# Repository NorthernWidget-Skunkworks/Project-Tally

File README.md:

# Project-Tally
A minimal ultra low power digital event counter, designed to be a counterpart to a traditional data logger to measure and average rapid events like an anemometer reading

## Features:
- On board super capacitor (can be self powered between readings/recharge) 
- Extreme low power 
- 3.3/5v capable 
- I2C interface
- Measure up to 65536 (2^16) events before rollover
- Integrated input pullup/pulldown
- Integrated input conditioning (allows for non-binary inputs)

Using jumpers on bottom side of board, can configure input as pullup, pulldown (ultra low power mode), or direct input if driving from another device

### Connectivity:
Device can easily be interfaced to using I2C at either 3.3v or 5v (logic and power). 

A library has been developed for interfacing with Arduino based devices:
[Tally Library](https://github.com/NorthernWidget-Skunkworks/Tally_Library)
### Power Consumption: 

| Mode | Current @ 3.3v | 
| ---- | ------------- |
| Default | ~4mA |
| Sleep | <100uA |
| Switched | N/A<sup>1</sup> |

<sup>1</sup>When the device is disconnected from the power bus, it draws no external power and runs off the on board super cap. Tested in pull up mode with 100Hz, 50% duty cycle switching input. Ran for 30 minutes, resulting in a consumption of ~ 0.275J of energy = 7.64e-5 Watt Hours -> 15.26 uW avg -> ~ 5uA @ 3v avg. 

#### Maximum input frequency: 

| Mode | Max Freq [kHz] | 
| ---- | ------------- |
| Pull Up | 16 |
| Pull Down | 10 |
| Direct, Square | 9 |
| Direct, Sine | 22 |
| Direct, Triangle | 22 |

Measured using a function generator with a 2.5v amplitude for push pull tests, and driving an appropriately selected MOSFET for the pull up and pull down variations to act as an analogous switch, once again driven by a function generator. 

---

> ##### ***"Errors using inadequate data are much less than those using no data at all."***
> - **[Charles Babbage](https://en.wikipedia.org/wiki/Charles_Babbage)**

**Concept and design by [Bobby Schulz](https://github.com/bschulz1701) at Northern Widget**

<br>
<br />This work is licensed under a <a rel="license" href="http://creativecommons.org/licenses/by-sa/4.0/">Creative Commons Attribution-ShareAlike 4.0 International License</a>.

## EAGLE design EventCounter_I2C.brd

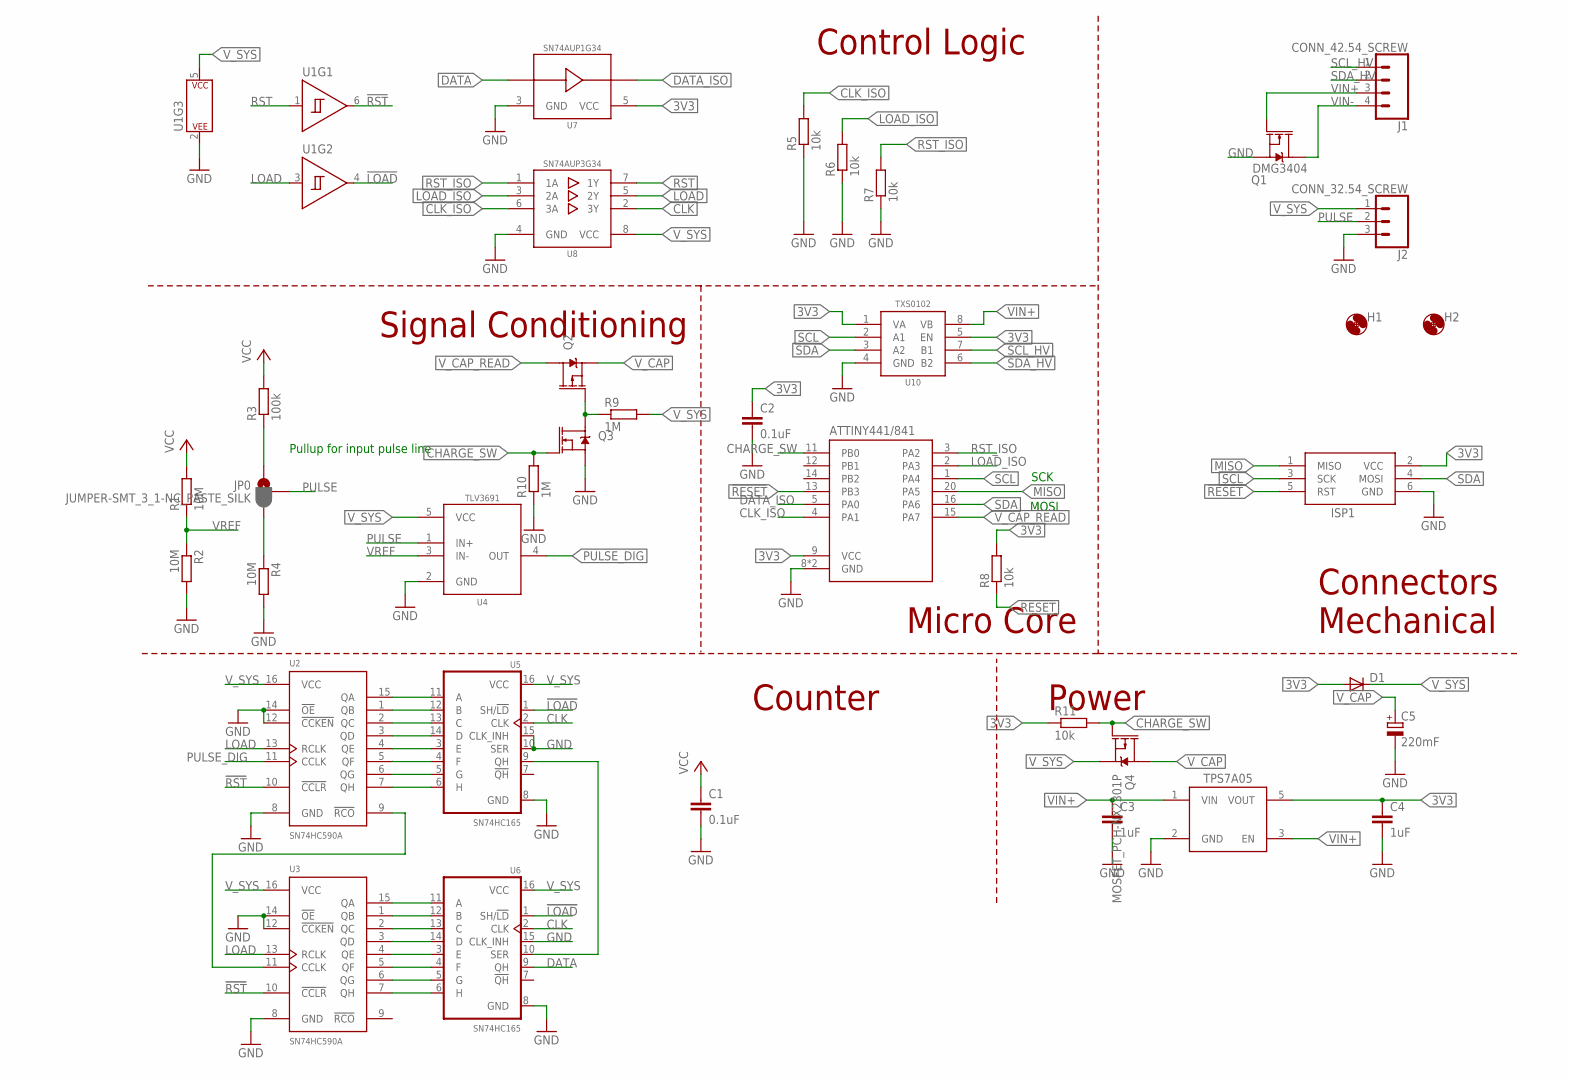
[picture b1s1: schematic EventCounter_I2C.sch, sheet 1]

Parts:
C1, C2: 0.1uF; C0402
C3, C4: 1uF; C0603
C5: 220mF; HL; MPN DSK-3R3H224U-HL; DIGIKEY 604-1020-1-ND
D1: DIODESOD-123; SOD-123; MPN BAT43W-7-F; DIGIKEY BAT43W-FDICT-ND
H1, H2: MOUNTING_HOLE2_NP; 2_56
ISP1: AVRISP1.27MM; 2X3_1.27
J1: CONN_42.54_SCREW; 1X04_SCREW
J2: CONN_32.54_SCREW; 1X03_SCREW
JP0: JUMPER-SMT_3_1-NC_PASTE_SILK; SMT-JUMPER_3_1-NC_PASTE_SILK
Q1: DMG3404; SOT23-3
Q2: MOSFET_PCH-RZM001P02; SOT723
Q3: MOSFET-NCH-RE1C002UN; SC-89
Q4: MOSFET_PCH-NX2301P; SOT23-3
R1, R2, R4: 10M; R0603
R3: 100k; R0603
R5, R6, R7, R8, R11: 10k; R0402
R9, R10: 1M; R0402
U1: SN74AUP2G14SC70; DCK_R-PDSO-G6
U2, U3: SN74HC590AD; SO16
U4: TLV3691DCK; DCK_R-PDSO-G5
U5, U6: SN74HC165PW; TSSOP16
U7: SN74AUP1G34SC70; DCK_R-PDSO-G5
U8: SN74AUP3G34DCU; DCU_(R-PDSO-G8)
U9: ATTINY441/841VQFN; VQFN-20
U10: TXS0102DQM; DQM_R-PX2SON-N8
U11: TPS7A0533DBV; SOT23-5

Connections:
3V3: C2.1, C4.1, D1.ANODE (A), ISP1.2 (VCC), R8.2, R11.1, U7.5 (VCC), U9.9 (VCC), U10.1 (VA), U10.5 (EN), U11.5 (VOUT)
!LOAD: U1.4 (Y), U5.1 (SH/!LD), U6.1 (SH/!LD)
!RESET: ISP1.5 (RST), R8.1, U9.13 (PB3)
!RST: U1.6 (Y), U2.10 (!CCLR), U3.10 (!CCLR)
CHARGE_SW: Q3.1 (G), Q4.1 (G), R10.2, R11.2, U9.11 (PB0)
CLK: U5.2 (CLK), U6.2 (CLK), U8.2 (3Y)
CLK_ISO: R5.2, U8.6 (3A), U9.4 (PA1)
DATA: U6.9 (QH), U7.2 (A)
DATA_ISO: U7.4 (Y), U9.5 (PA0)
GND: C1.2, C2.2, C3.2, C4.2, C5.-, ISP1.6 (GND), J2.3, Q1.2 (S), Q3.2 (S), R2.2, R4.2, R5.1, R6.1, R7.1, R10.1, U1.2 (P$V-), U2.8 (GND), U2.12 (!CCKEN), U2.14 (!OE), U3.8 (GND), U3.12 (!CCKEN), U3.14 (!OE), U4.2 (GND), U5.8 (GND), U5.10 (SER), U5.15 (CLK_INH), U6.8 (GND), U6.15 (CLK_INH), U7.3 (GND), U8.4 (GND), U9.8 (GND), U9.EP (GND), U10.4 (GND), U11.2 (GND)
LOAD: U1.3 (A), U2.13 (RCLK), U3.13 (RCLK), U8.5 (2Y)
LOAD_ISO: R6.2, U8.3 (2A), U9.2 (PA3)
MISO: ISP1.1 (MISO), U9.20 (PA5)
unnamed: U3.15 (QA), U6.11 (A)
unnamed: U3.1 (QB), U6.12 (B)
unnamed: U3.2 (QC), U6.13 (C)
unnamed: U3.3 (QD), U6.14 (D)
unnamed: U3.4 (QE), U6.3 (E)
unnamed: U3.5 (QF), U6.4 (F)
unnamed: U3.6 (QG), U6.5 (G)
unnamed: U3.7 (QH), U6.6 (H)
unnamed: U2.7 (QH), U5.6 (H)
unnamed: U2.6 (QG), U5.5 (G)
unnamed: U2.5 (QF), U5.4 (F)
unnamed: U2.4 (QE), U5.3 (E)
unnamed: U2.3 (QD), U5.14 (D)
unnamed: U2.2 (QC), U5.13 (C)
unnamed: U2.1 (QB), U5.12 (B)
unnamed: U2.15 (QA), U5.11 (A)
unnamed: U5.9 (QH), U6.10 (SER)
unnamed: U2.9 (!RCO), U3.11 (CCLK)
unnamed: JP0.3, R4.1
unnamed: JP0.1, R3.1
unnamed: Q2.1 (G), Q3.3 (D), R9.1
PULSE: J2.2, JP0.2, U4.1 (IN+)
PULSE_DIG: U2.11 (CCLK), U4.4 (OUT)
RST: U1.1 (A), U8.7 (1Y)
RST_ISO: R7.2, U8.1 (1A), U9.3 (PA2)
SCL: ISP1.3 (SCK), U9.1 (PA4), U10.2 (A1)
SCL_HV: J1.1, U10.7 (B1)
SDA: ISP1.4 (MOSI), U9.16 (PA6), U10.3 (A2)
SDA_HV: J1.2, U10.6 (B2)
VIN+: C3.1, J1.3, Q1.1 (G), U10.8 (VB), U11.1 (VIN), U11.3 (EN)
VIN-: J1.4, Q1.3 (D)
VREF: R1.1, R2.1, U4.3 (IN-)
V_CAP: C5.+, Q2.2 (S), Q4.3 (D)
V_CAP_READ: Q2.3 (D), U9.15 (PA7)
V_SYS: C1.1, D1.CAT (C), J2.1, Q4.2 (S), R1.2, R3.2, R9.2, U1.5 (P$V+), U2.16 (VCC), U3.16 (VCC), U4.5 (VCC), U5.16 (VCC), U6.16 (VCC), U8.8 (VCC)

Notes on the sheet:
Pullup for input pulse line
Counter
Control Logic
Connectors Mechanical
MOSI
SCK
Power
Micro Core
Signal Conditioning

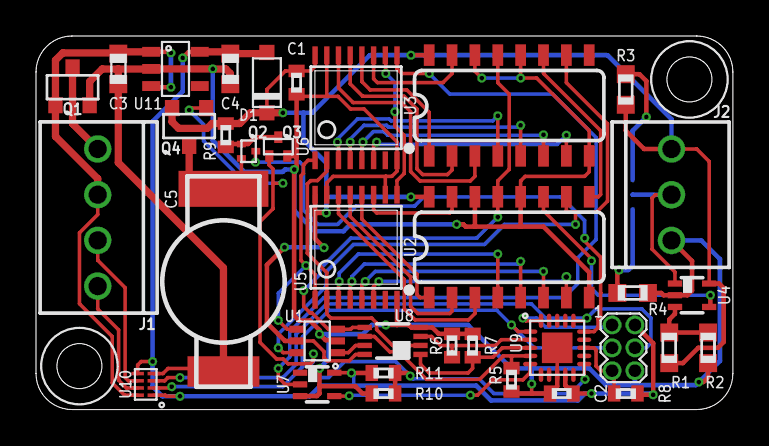
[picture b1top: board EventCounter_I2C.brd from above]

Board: 2 copper layers, 38.7 x 20.8 mm, 38 parts (1 on the bottom side), 48 nets.

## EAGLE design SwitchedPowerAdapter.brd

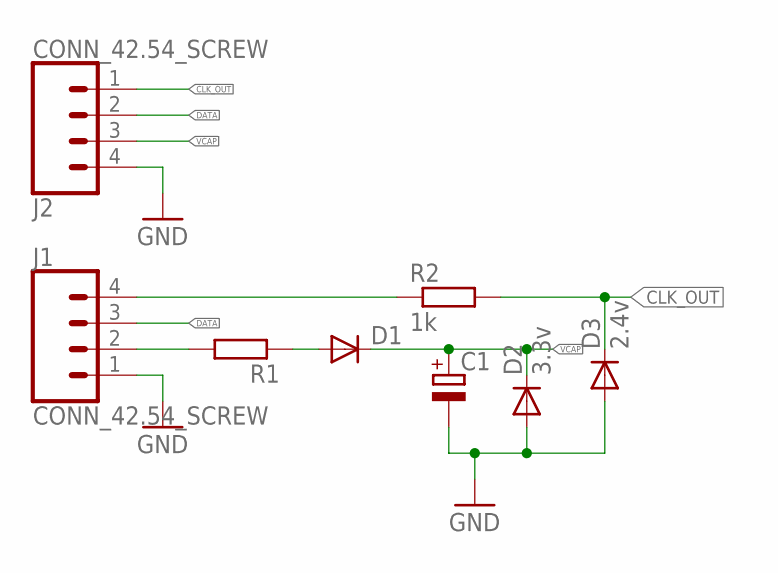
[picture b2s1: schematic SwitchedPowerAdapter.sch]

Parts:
C1: CPOL-EUHL; HL
D1: DIODEDO-214AC; DO214AC; MPN S1A; DIGIKEY S1AFSCT-ND
D2: 3.3v; SOD-123; MPN MMSZ4683-HE3-08; DIGIKEY MMSZ4683-HE3-08GICT-ND
D3: 2.4v; SOD-123
J1, J2: CONN_42.54_SCREW; 1X04_SCREW
R1: R-EU_R2512; R2512
R2: 1k; R0402

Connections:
CLK: J1.4, R2.1
CLK_OUT: D3.CAT (C), J2.1, R2.2
DATA: J1.3, J2.2
GND: C1.-, D2.ANODE (A), D3.ANODE (A), J1.1, J2.4
unnamed: J1.2, R1.2
unnamed: D1.A, R1.1
VCAP: C1.+, D1.C, D2.CAT (C), J2.3

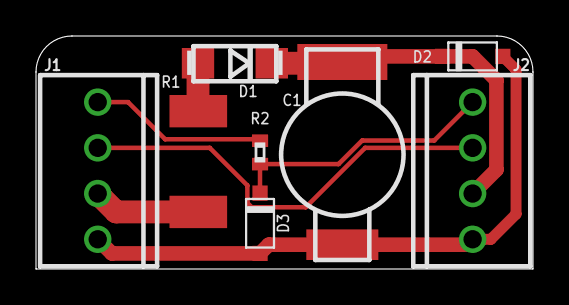
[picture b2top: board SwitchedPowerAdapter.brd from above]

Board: 2 copper layers, 27.6 x 12.9 mm, 8 parts (0 on the bottom side), 7 nets.

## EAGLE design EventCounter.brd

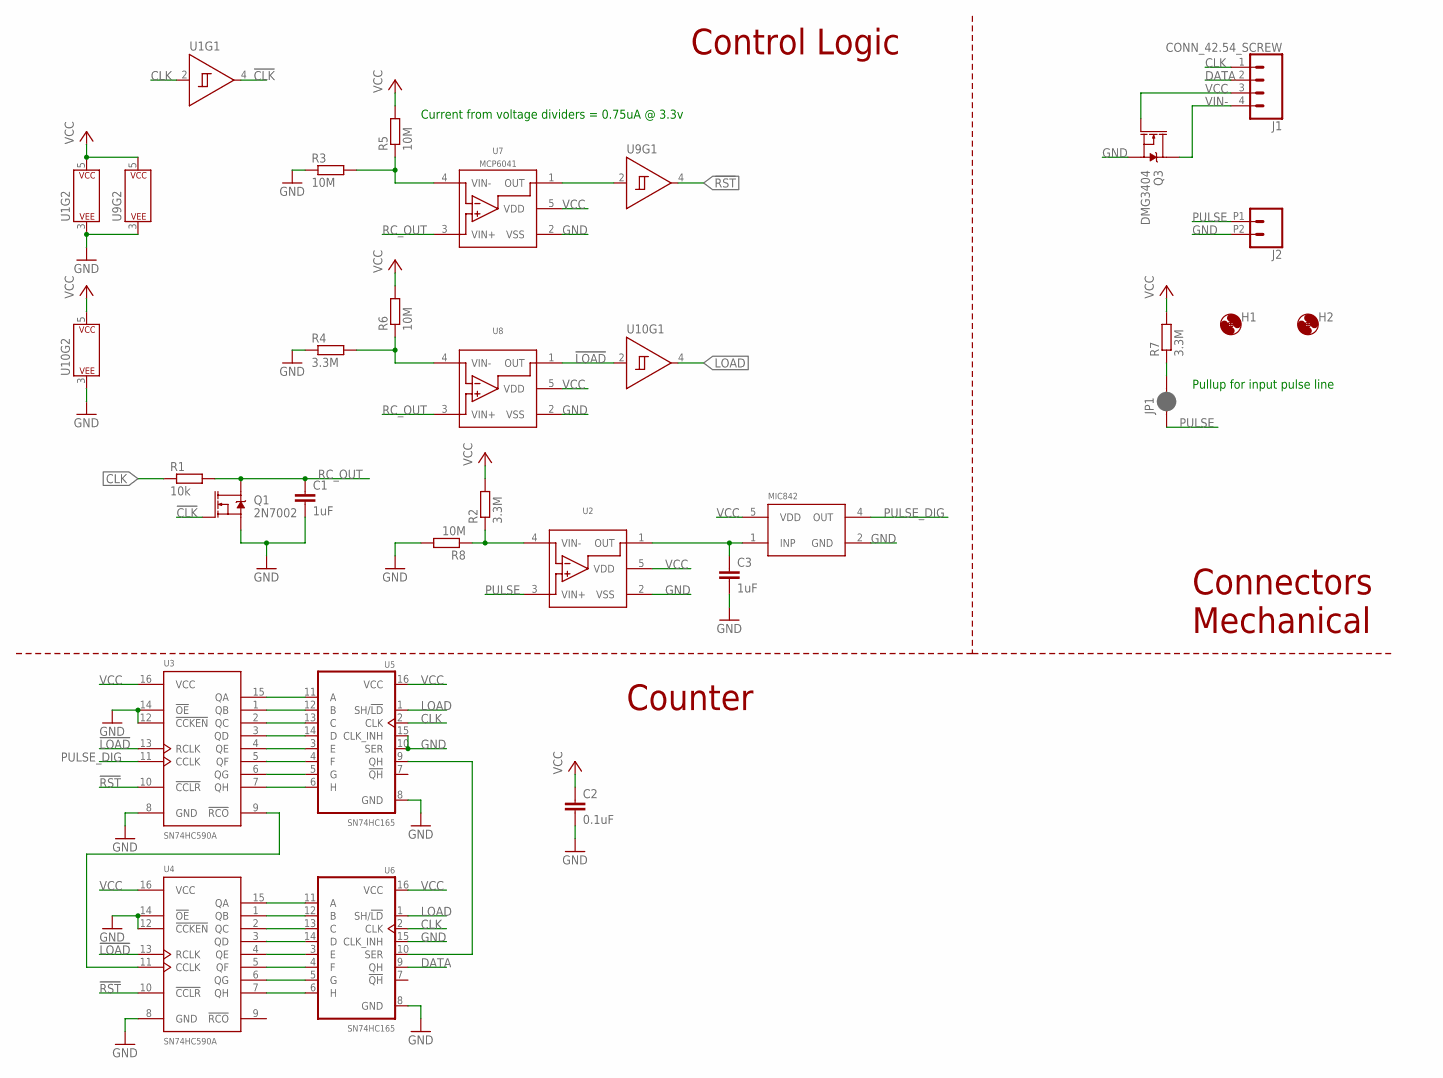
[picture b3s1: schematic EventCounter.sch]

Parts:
C1, C3: 1uF; C0603
C2: 0.1uF; C0603
H1, H2: MOUNTING_HOLE2_NP; 2_56
J1: CONN_42.54_SCREW; 1X04_SCREW
J2: CONN_02SCREW_2.54; 1X02_2.54_SCREWTERM
JP1: JUMPER-SMT_2_NC_PASTE_SILK; SMT-JUMPER_2_NC_PASTE_SILK
Q1: 2N7002; SOT323
Q3: DMG3404; SOT23-3
R1: 10k; R0603
R2, R4, R7: 3.3M; R0603
R3, R5, R6, R8: 10M; R0603
U1, U9, U10: SN74LVC1G14DCK; DCK_R-PDSO-G5
U2, U7, U8: MCP6041; SOT23-5
U3, U4: SN74HC590AD; SO16
U5, U6: SN74HC165D; SO16
U$1: MIC842H; DCK_R-PDSO-G5

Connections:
!CLK: Q1.1 (G), U1.4 (Y)
!LOAD: U3.13 (RCLK), U4.13 (RCLK), U8.1 (OUT), U10.2 (A)
!RST: U3.10 (!CCLR), U4.10 (!CCLR), U9.4 (Y)
CLK: J1.1, R1.1, U1.2 (A), U5.2 (CLK), U6.2 (CLK)
DATA: J1.2, U6.9 (QH)
GND: C1.2, C2.2, C3.2, J2.P2 (2), Q1.2 (S), Q3.2 (S), R3.1, R4.1, R8.2, U1.3 (P$V-), U2.2 (VSS), U3.8 (GND), U3.12 (!CCKEN), U3.14 (!OE), U4.8 (GND), U4.12 (!CCKEN), U4.14 (!OE), U5.8 (GND), U5.10 (SER), U5.15 (CLK_INH), U6.8 (GND), U6.15 (CLK_INH), U7.2 (VSS), U8.2 (VSS), U9.3 (P$V-), U10.3 (P$V-), U$1.2 (GND)
LOAD: U5.1 (SH/!LD), U6.1 (SH/!LD), U10.4 (Y)
unnamed: U4.15 (QA), U6.11 (A)
unnamed: U4.1 (QB), U6.12 (B)
unnamed: U4.2 (QC), U6.13 (C)
unnamed: U4.3 (QD), U6.14 (D)
unnamed: U4.4 (QE), U6.3 (E)
unnamed: U4.5 (QF), U6.4 (F)
unnamed: U4.6 (QG), U6.5 (G)
unnamed: U4.7 (QH), U6.6 (H)
unnamed: U3.7 (QH), U5.6 (H)
unnamed: U3.6 (QG), U5.5 (G)
unnamed: U3.5 (QF), U5.4 (F)
unnamed: U3.4 (QE), U5.3 (E)
unnamed: U3.3 (QD), U5.14 (D)
unnamed: U3.2 (QC), U5.13 (C)
unnamed: U3.1 (QB), U5.12 (B)
unnamed: U3.15 (QA), U5.11 (A)
unnamed: U5.9 (QH), U6.10 (SER)
unnamed: U3.9 (!RCO), U4.11 (CCLK)
unnamed: R2.1, R8.1, U2.4 (VIN-)
unnamed: JP1.2, R7.1
unnamed: R4.2, R6.1, U8.4 (VIN-)
unnamed: C3.1, U2.1 (OUT), U$1.1 (INP)
unnamed: R3.2, R5.1, U7.4 (VIN-)
PULSE: J2.P1 (1), JP1.1, U2.3 (VIN+)
PULSE_DIG: U3.11 (CCLK), U$1.4 (OUT)
RC_OUT: C1.1, Q1.3 (D), R1.2, U7.3 (VIN+), U8.3 (VIN+)
RST: U7.1 (OUT), U9.2 (A)
VCC: C2.1, J1.3, Q3.1 (G), R2.2, R5.2, R6.2, R7.2, U1.5 (P$V+), U2.5 (VDD), U3.16 (VCC), U4.16 (VCC), U5.16 (VCC), U6.16 (VCC), U7.5 (VDD), U8.5 (VDD), U9.5 (P$V+), U10.5 (P$V+), U$1.5 (VDD)
VIN-: J1.4, Q3.3 (D)

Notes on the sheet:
Pullup for input pulse line
Counter
Control Logic
Connectors Mechanical
Current from voltage dividers = 0.75uA @ 3.3v

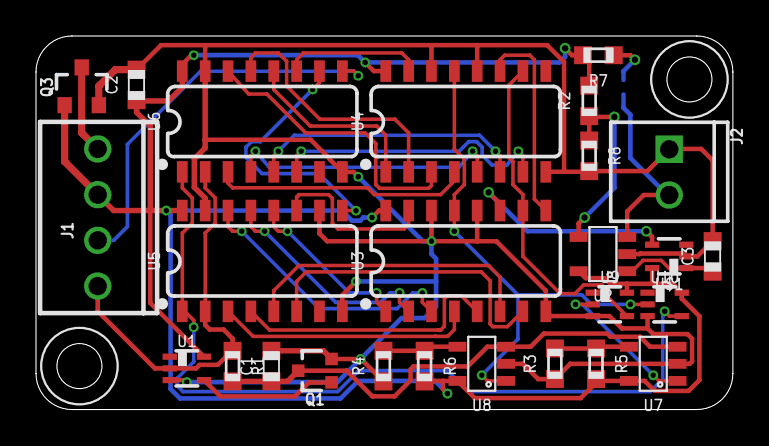
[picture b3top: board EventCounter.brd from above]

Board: 2 copper layers, 38.7 x 20.8 mm, 29 parts (1 on the bottom side), 36 nets.

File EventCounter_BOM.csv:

"Qty";"Value";"Device";"Package";"Parts";"Description";"DIGIKEY";"DISP";"MF";"MPN";"PROD_ID";"VALUE";"VALUE_PART";
"1";"";"CONN_02SCREW_2.54";"1X02_2.54_SCREWTERM";"J2";"Multi connection point. Often used as Generic Header-pin footprint for 0.1 inch spaced/style header connections";"ED10561-ND";"";"OnShore";"OSTVN02A150";"";"";"";
"2";"";"MOUNTING_HOLE2_NP";"2_56";"H1, H2";"Genaric Mechanical Mounting Hole";"";"";"";"";"";"";"";
"2";"";"SN74HC165D";"SO16";"U5, U6";"SN74HC165 - 8 bit PISO shift register";"296-8250-1-ND";"";"TI";"SN74HC165DR";"";"";"";
"2";"";"SN74HC590AD";"SO16";"U3, U4";"SN74HC590A - 8 bit binary counter with direct clear";"296-8340-5-ND";"";"TI";"SN74HC590AD";"";"";"";
"3";"";"SN74LVC1G14DCK";"DCK_R-PDSO-G5";"U1, U9, U10";"SN74x1G14 - Single Schmitt Triger Inverter";"296-11608-1-ND";"";"TI";"SN74LVC1G14DCKR";"";"";"";
"1";"0.1uF";"C-EU0.1UFC0603";"C0603";"C2";"CAPACITOR, European symbol";"490-6051-1-ND";"";"Murata";"GCM188R71E104KA57D";"";"";"";
"3";"10M";"R-EU_10MR0603";"R0603";"R3, R5, R6";"RESISTOR, European symbol";"311-10.0MHRCT-ND";"";"Yageo";"RC0603FR-0710ML";"";"";"10M";
"2";"10k";"R-EU_10KR0603";"R0603";"R1, R7";"RESISTOR, European symbol";"311-10.0KHRCT-ND";"";"Yageo";"RC0603FR-0710KL";"";"";"10k";
"1";"1uF";"C-EU1UFC0603";"C0603";"C1";"CAPACITOR, European symbol";"1276-6524-1-ND";"";"Samsung";"1276-6524-1-ND";"";"";"";
"1";"2N7002";"MOSFET-NCH-2N7002PW";"SOT323";"Q1";"N-channel MOSFETs";"2N7002W-FDICT-ND";"";"Diodes Incorporated";"2N7002W-7-F";"TRANS-11151";"2N7002";"";
"1";"3.3M";"R-EU_3.3MR0603";"R0603";"R4";"RESISTOR, European symbol";"RMCF0603FT3M30CT-ND";"";"Stackpole";"RMCF0603FT3M30";"";"";"3.3M";
"1";"CONN_42.54_SCREW";"CONN_42.54_SCREW";"1X04_SCREW";"J1";"Genaric 4 pin connector";"";"";"";"";"";"";"";
"1";"DMG3404";"MOSFET-NCH-DMG3404L";"SOT23-3";"Q3";"N-channel MOSFETs";"DMG3404L-7DICT-ND";"";"Diodes Incorporated";"DMG3404L-7";"";"DMG3404";"";
"1";"JUMPER-SMT_2_NC_PASTE_SILK";"JUMPER-SMT_2_NC_PASTE_SILK";"SMT-JUMPER_2_NC_PASTE_SILK";"JP1";"Normally closed solder jumper";"";"";"";"";"";"";"";
"2";"MCP6041";"MCP6041";"SOT23-5";"U7, U8";"MCP6041 - Low Power Rail to Rail Op-Amp";"MCP6041T-I/OTCT-ND";"MCP6041";"Microchip";"MCP6041T-I/OT";"";"";"";

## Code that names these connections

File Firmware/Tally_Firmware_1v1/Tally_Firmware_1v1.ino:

/******************************************************************************
Tally_Firmware_1v1.ino
Driver for Tally event counter
Bobby Schulz @ Northern Widget LLC
5/16/2019
https://github.com/NorthernWidget-Skunkworks/Project-Tally

This firmware is to be run on the I2C capable Tally v1.1 in order to allow for interface, control, and data collection 

Firmware Version: 0.2.0

"On two occasions I have been asked, 'Pray, Mr. Babbage, if you put into the machine wrong figures, will the right answers come out?' 
I am not able rightly to apprehend the kind of confusion of ideas that could provoke such a question."
-Charles Babbage

Distributed as-is; no warranty is given.
******************************************************************************/

#include <avr/sleep.h>
#include <avr/power.h>
#include <avr/interrupt.h>
#include "WireS.h"
#define DATA_PIN 10
#define CLK_PIN 9
#define RST_PIN 8
#define LOAD_PIN 7
#define CHARGE_SW 0
#define V_CAP_READ A7

#define CHIP_ID_CALL 0xD0
#define CHIP_ID 0xB0
#define FIRMWARE_NUM 2

uint8_t ADR = 0x33; //DUMMY! FIX! and make changable

// volatile bool GenCall = false; //Flag for generic address call over I2C //FIX! add generalizable address

uint8_t Config = 0; //Global config value
uint8_t Reg[5] = {0}; //Initialize registers
const uint8_t RegLen = sizeof(Reg); //Number of registers in Reg
bool Sample = false; //Flag to get a new sample value
bool Reset = false; //Reset flag
bool Clear = false; //Clear registers
bool Peek = false; //Clear values on read by default
bool Sleep = false; //Do not sleep by default
bool ReadCap = false; //Read float voltage of capacitor 
bool NoCap = false; //Disconnect capacitor, this will be reset on POR

volatile bool StopFlag = false; //Used to indicate a stop condition 
volatile uint8_t RegID = 0; //Used to denote which register will be read from
volatile bool RepeatedStart = false; //Used to show if the start was repeated or not

const unsigned long WAIT_TIME = 100; //Genric wait cycle after read operation, keep device alive for repeated requests

void setup() {
	pinMode(DATA_PIN, INPUT); //Setup GPIO interface pins
	pinMode(CLK_PIN, OUTPUT);
	pinMode(RST_PIN, OUTPUT);
	pinMode(LOAD_PIN, OUTPUT);
	pinMode(CHARGE_SW, OUTPUT);
	ReadVoltage(); //Get voltage on startup, available to read afterwards 
	digitalWrite(CHARGE_SW, LOW); //By default have system charging 

	Wire.begin(ADR);  //Begin slave I2C FIX! Add variable address feature!

	//Setup I2C slave
	Wire.onAddrReceive(AddressEvent); 
	Wire.onRequest(RequestEvent);    
	Wire.onReceive(ReceiveEvent);
	Wire.onStop(StopEvent);
}

void loop() {

	if(Sleep) { //Put device to sleep on wrap arround
		ADCSRA &= ~(1<<ADEN); //Disable ADC
		SPCR   &= ~_BV(SPE); //Disable SPI
		//    PRR = 0xFF;
			set_sleep_mode(SLEEP_MODE_PWR_DOWN);  

		sleep_enable();
		sleep_mode(); //Waits here while in sleep mode

		sleep_disable(); //Wake up
		TWSCRA = bit(TWEN);  //Re-enable I2C
		Wire.begin(ADR);
	}

	int Counter = 0; //Run cycles after wakeup
	while(++Counter < WAIT_TIME) {
		Sample = BitRead(Reg[0], 0);
		Clear = BitRead(Reg[0], 1);
		Reset = BitRead(Reg[0], 2);
		Peek = BitRead(Reg[0], 3);
		Sleep = BitRead(Reg[0], 4); 
		ReadCap = BitRead(Reg[0], 5);
		NoCap = BitRead(Reg[0], 6);

		if(Sample) {
			SplitAndLoad(1, GetTicks()); //Load tick value into register 1
			if(!Peek) ClearTicks(); //Clear counter values if peak is disabled
			Reg[0] = Reg[0] & 0xFE; //Clear sample bit in register
			Sample = false; //Clear sample bit
		}
		if(Reset) { //Software reset of system
			ClearTicks();
			Reg[1] = 0x00; //Clear registers
			Reg[2] = 0x00;
			Reg[0] = Reg[0]; //Reset to POR
			Clear = false; //Clear flag
		}
		if(Clear) {
			ClearTicks(); //Clear registers 
			Reg[0] = Reg[0] & 0xFD; //Clear CLEAR bit
			Reset = false; //Clear flag
		}

		if(ReadCap) {
			ReadVoltage(); //Read voltage and load into I2C regs
			Reg[0] = Reg[0] & 0xDF; //Clear Voltage Read bit
			ReadCap = false; //Clear flag
		}

		if(NoCap) {
			digitalWrite(CHARGE_SW, HIGH); //Disconnect cap from Vin
		}

		if(!NoCap) {
			digitalWrite(CHARGE_SW, LOW); //Connect cap to Vin
		}
		delay(1); //Wait during wake/I2C transaction 
	}
	Counter = 0; //Clear counter to either go to sleep or wrap around
}

void SplitAndLoad(uint8_t Pos, unsigned int Val) //Write 16 bits
{
	uint8_t Len = sizeof(Val);
	for(int i = Pos; i < Pos + Len; i++) {
		Reg[i] = (Val >> (i - Pos)*8) & 0xFF; //Pullout the next byte
	}
}

boolean AddressEvent(uint16_t Address, uint8_t count) //When a valid address is encountered on I2C
{
	// if(Address == 0x00) { //FIX! add generalizable address
	// 	GenCall = true;
	// }
	RepeatedStart = (count > 0 ? true : false);
	return true; // send ACK to master
}

void RequestEvent()  //When I2C values are requested
{	if(RegID == CHIP_ID_CALL) {
		Wire.write(CHIP_ID); //Return Chip ID if requested
		Wire.write(FIRMWARE_NUM); //Send firmware version number
	}
	else {
		for(int i = 0; i < RegLen; i++) {  
			Wire.write(Reg[(RegID + i) % RegLen]);  //Load all bytes (wrap around) into register
		}
	}
}

void ReceiveEvent(int DataLen) //When I2C values are sent 
{
    //Write data to appropriate location
    if(DataLen == 2){
	    //Remove while loop?? 
	    while(Wire.available() < 2); //Only option for writing would be register address, and single 8 bit value
	    uint8_t Pos = Wire.read();
	    uint8_t Val = Wire.read();
	    //Check for validity of write??
	    Reg[Pos] = Val; //Set register value
	}

	// if(DataLen == 1 && GenCall == true) {  //FIX! add generalizable address
	// 	ADR = Wire.read(); //Update address value 
	// }

	// if(DataLen == 1 && GenCall == false){
	// 	RegID = Wire.read(); //Read in the register ID to be used for subsequent read
	// }
	if(DataLen == 1){
		RegID = Wire.read(); //Read in the register ID to be used for subsequent read
	}
}

void StopEvent() //When stop value is detected on I2C
{
	StopFlag = true;
  	RegID = (RegID + Wire.getTransmitBytes()) % RegLen; //Increment register pointer appropriate amount
	//End comunication
}

unsigned int GetTicks() //Read number of ticks from digital logic 
{
	unsigned int Data = 0; //Number of pulses since last read
	digitalWrite(LOAD_PIN, HIGH);  //Pulse LOAD pin low to trigger load of new data
	delayMicroseconds(5); 
  	digitalWrite(LOAD_PIN, LOW); 

  	Data = digitalRead(DATA_PIN);
  	Data = Data << 1; 
	for(int i = 0; i < 15; i++) {
    digitalWrite(CLK_PIN, HIGH); //Clock new data in
		delayMicroseconds(5); //Wait to stabilize
		Data = (Data << 1) | digitalRead(DATA_PIN);
    digitalWrite(CLK_PIN, LOW); 
		delayMicroseconds(5);
	} 
	return Data;
}

void ClearTicks() //Clear digital logic values 
{
	digitalWrite(RST_PIN, HIGH);  //Pulse reset pin high for short interval to trigger reset
	delayMicroseconds(5);
  	digitalWrite(RST_PIN, LOW); 
}

bool ReadVoltage() //Read the bit value at the specified position
{
	digitalWrite(CHARGE_SW, HIGH); //Connect voltage to ADC
	delay(1); //Wait to settle FIX??
	uint16_t Val = analogRead(V_CAP_READ);
	if(!NoCap) digitalWrite(CHARGE_SW, LOW); //Disconnect and continue charging if cap is set to be nominally connected
	Reg[4] = Val >> 8; //Load MSB
	Reg[3] = Val & 0xFF; //Load LSB
}

bool BitRead(uint8_t Val, uint8_t Pos) //Read the bit value at the specified position
{
	return (Val >> Pos) & 0x01;
}

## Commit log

2018-05-22 WIP simulations for control circuitry
2018-05-22 Added simulations for new pulse length trigger
    Added simulations for some of the legacy designs for the pulse length trigger, and the new design for pulse length trigger with Monte Carlo simulations
2018-05-23 Added schematic for event counter with preliminary layout
    Schematic is essentially complete, very preliminary part placement done on board
2018-05-23 Cleaned up schematic and added frame
2018-05-24 Completed initial routing, added silk screen info
    Board is functionally complete baring cleanup or modifications, added silk screen info to bottom layer
2018-05-24 Changed passive values
    Changed the passive resistor divider values, need to verify with part availability
2018-05-25 Changed resistor divider values for low power
    After checking part availability, changed values to more logical ones
2018-06-01 Simulation cleanup
2018-06-05 Added BOM and decoupling cap
    Added BOM files and decoupling capacitor, cleaned up some silkscreen issues, ready for final review
2018-06-06 Added Gerbers, ready for first run
    Did cleanup and added reverse polarity symbol, generated gerbers, also updated gitignore to deal with LTSpice files
2018-06-28 Added input signal conditioning, added test script
    Added input signal conditioning to fix metastability problem occurring due to excessive rise times due to pullup input
2018-06-28 Updated part info, license and BOM
2018-07-10 Updated gerbers
2018-07-12 Added wind tunnel test file, needs further verification
2018-07-17 Added stencil DXF
2018-11-08 Initial layout of capacitor charge board
    Early layout of external capacitor charge board
2018-11-27 Generated gerbers, updated part number on Switched Power
2019-01-04 Const Power Adapter minor edits, generated gerbers
    Minor edits to silkscreen on Const Power Adapter and generated gerbers, submitted adapter board v0.0 to fab
2019-04-08 Added testing data and updated TallyTest to support power switching
2019-04-08 Added board dimensions and generated PDFs
2019-04-18 Added initial developments for I2C variant
    Added first cut schematic for I2C variant, needs verification and decent cleanup
2019-04-19 Initial layout for I2C variant
    First cut layout for I2C variant, passes DRC, still needs verification
2019-04-20 Minor edits, sent to fab for v1.0 (I2C model)
    Cleaned up layout, added pullup reset resistor, generated gerbers, sent v1.0 to fab
2019-04-21 Rename LICENSE.md to LICENSE
2019-04-21 CC BY-SA 4.0 International: official wording
2019-04-30 Updated values/digikey info
    Updated the part
2019-05-15 Updated firmware, minor design update
    Improved firmware capabilities, added minor design updates to schematic, routing and feature decision still required
2019-05-15 Routing and design update for v1.1
    Cleanup/verification required before sending to fab
2019-05-16 Minor cleanup, generated gerbers, sent v1.1 to fab
    Minor cleanup and rearranging silkscreen names, changed jumper configuration
2019-05-16 Firmware cleanup
2019-05-27 Added support for v1.2 I2C board in firmware
    Added support for voltage reading on the v1.2 I2C board, still need to rename/organize firmware
2019-05-29 Updated voltage read in firmware
    Added voltage read on startup, so you can read minimum voltage after cycle is completed
2019-06-06 Minor value updates
2019-06-13 Updated part values
    Switched values of `R10` and `R11`, values were erroneously switched which resulted in the capacitor being connected to the ADC input during sleep/off state, causing significant power draw
2019-06-27 Minor readme addition
2019-06-28 Updated readme with valid info
    Needs verification/correction on frequency values
2019-06-28 Updated frequency values in readme
2019-06-28 Initial test of ChipID implementation
    Testing required
2019-06-28 Attempted gitignore tracking fix
2019-06-28 Re-added CSVs, reorganized folder structure
2019-06-28 Moved regmap info into firmware folder
2019-06-28 Updated readme, added switched cap support in firmware
    Added support for switched capacitor and changed naming of `reset` and `clear` to match that of software library
2019-06-28 Updated readme with test info
2019-07-03 Added firmware report
2020-04-30 Stencil flat surface for solder-paste application
2020-05-01 Definitely not noncommercial; wrong text in license file!
2020-05-01 GNU GPL v3 for code products (software, firmware, etc.)
2022-09-28 Zenodo DOI badge
2022-09-28 Schulz 2020
2022-10-13 Linear fit to anemometer + wind tunnel data
2022-10-13 Local README with anemometer fit parameters

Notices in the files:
parts and their libraries:
SparkFun-Jumpers: Licensing: Creative Commons ShareAlike 4.0 International - https://creativecommons.org/licenses/by-sa/4.0
bschulz: This work is licensed under the Creative Commons Attribution-ShareAlike 4.0
